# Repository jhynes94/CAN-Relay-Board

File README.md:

# CAN-Relay-Board
CAN controlled Relay board for automotive applications

## Items to complete
1. Detemine Relay to use for design (based on Current(A)/Costs constraints).
2. Design better interface board to use Arduino Nano Programmer
    1. JST Connector to Arduino Development Board
    2. 2.54mm Connector with standard interface board
    3. Consider adding UART connector as well.
3. Determine modes needed for device
    1. CAN ID changing?
    2. CAN Mode changing?
    3. How this should be modified? (DIP swich or via SW)

## Development Setup

Programming the ATTiny is a bit difficult. Setup can be completed using the following tutorial:
https://youtu.be/AL9vK_xMt4E

The library used for SPI enabled CAN device:
https://github.com/autowp/arduino-mcp2515

PEAK CAN usb device is used for interfacing and development. The software to run this is called <b>pcanview<b>

## Far Future items

Future Tutorial for programming an alternative way:
https://www.youtube.com/watch?v=ra7bT74EGUs

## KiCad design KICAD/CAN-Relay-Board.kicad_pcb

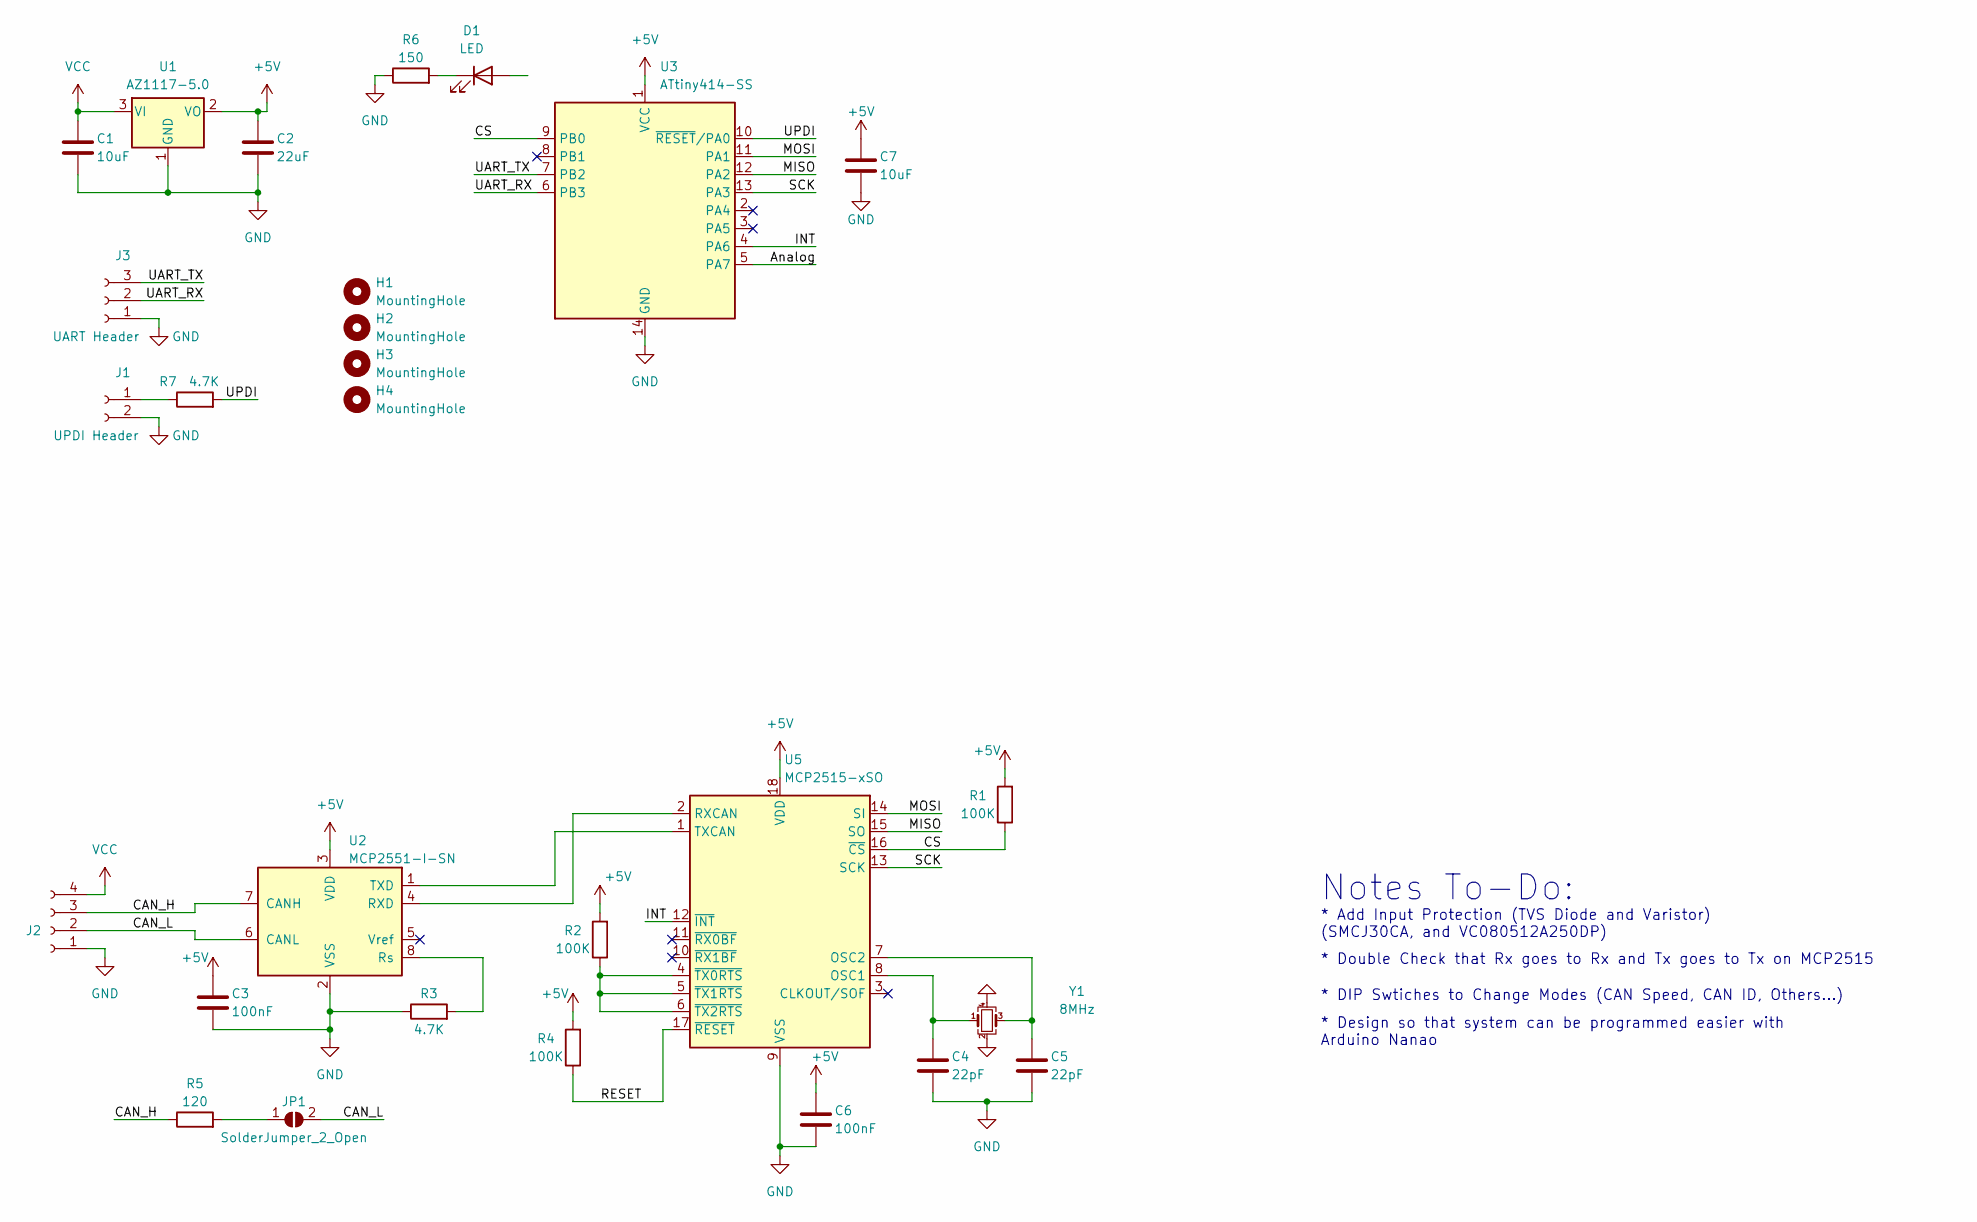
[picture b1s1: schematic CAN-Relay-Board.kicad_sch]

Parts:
C1, C7: 10uF; C_0805_2012Metric_Pad1.18x1.45mm_HandSolder; Manufacturer PN CL21A106KOQNNNE; Digi-Key PN 1276-1096-2-ND
C2: 22uF; C_0805_2012Metric_Pad1.18x1.45mm_HandSolder; Manufacturer PN CL21A226MOCLRNC; Digi-Key PN 1276-6780-1-ND
C3, C6: 100nF; C_0603_1608Metric_Pad1.08x0.95mm_HandSolder; Manufacturer PN CL10B104KB8NNNC; Digi-Key PN 1276-1000-1-ND
C4, C5: 22pF; C_0603_1608Metric_Pad1.08x0.95mm_HandSolder; Manufacturer PN CC0603JRNPO9BN220; Digi-Key PN 311-1062-1-ND
D1: LED; LED_0603_1608Metric_Pad1.05x0.95mm_HandSolder; Manufacturer PN LTST-C191KGKT; Digi-Key PN 160-1446-1-ND
H1, H2, H3, H4: MountingHole; MountingHole_2.2mm_M2_ISO14580
J1: UPDI Header; PinHeader_1x02_P1.27mm_Vertical
J2: Conn_01x04_Female; PinHeader_1x04_P1.27mm_Vertical
J3: UART Header; PinHeader_1x03_P1.27mm_Vertical
JP1: SolderJumper_2_Open; SolderJumper-2_P1.3mm_Open_TrianglePad1.0x1.5mm
R1, R2, R4: 100K; R_0603_1608Metric_Pad0.98x0.95mm_HandSolder; Manufacturer PN RC0603FR-07100KL; Digi-Key PN 311-100KHRCT-ND
R3, R7: 4.7K; R_0603_1608Metric_Pad0.98x0.95mm_HandSolder; Manufacturer PN RC0402JR-074K7L; Digi-Key PN 311-4.7KJRCT-ND
R5: 120; R_1206_3216Metric_Pad1.30x1.75mm_HandSolder; Manufacturer PN AC1206FR-07120RL; Digi-Key PN YAG3810CT-ND
R6: 150; R_0603_1608Metric_Pad0.98x0.95mm_HandSolder; Manufacturer PN RC0603FR-07150RL; Digi-Key PN 311-150HRCT-ND
U1: AZ1117-5.0; SOT-223-3_TabPin2; Manufacturer PN AZ1117IH-5.0TRG1; Digi-Key PN AZ1117IH-5.0TRG1DICT-ND
U2: MCP2551-I-SN; SOIC-8_3.9x4.9mm_P1.27mm
U3: ATtiny414-SS; SOIC-14_3.9x8.7mm_P1.27mm; Manufacturer PN ATTINY414-SSNR; Digi-Key PN ATTINY414-SSNRCT-ND
U5: MCP2515-xSO; SOIC-18W_7.5x11.6mm_P1.27mm; Manufacturer PN MCP2515-I/SO; Digi-Key PN MCP2515-I/SO-ND
Y1: 8MHz; Crystal_SMD_3225-4Pin_3.2x2.5mm_HandSoldering; Manufacturer PN ECS-80-8-33-JEN-TR3; Digi-Key PN 50-ECS-80-8-33-JEN-TR3CT-ND

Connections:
+5V: C2.1, C3.1, C6.1, C7.1, R1.2, R2.2, R4.2, U1.2 (VO), U2.3 (VDD), U3.1 (VCC), U5.18 (VDD)
/Analog: U3.5 (PA7)
/CAN_H: J2.3, R5.1, U2.7 (CANH)
/CAN_L: J2.2, JP1.2 (B), U2.6 (CANL)
/CS: R1.1, U3.9 (PB0), U5.16 (~CS)
/INT: U3.4 (PA6), U5.12 (~INT)
/MISO: U3.12 (PA2), U5.15 (SO)
/MOSI: U3.11 (PA1), U5.14 (SI)
/RESET: R4.1, U5.17 (~RESET)
/SCK: U3.13 (PA3), U5.13 (SCK)
/UART_RX: J3.2, U3.6 (PB3)
/UART_TX: J3.3, U3.7 (PB2)
/UPDI: R7.2, U3.10 (~RESET/PA0)
GND: C1.2, C2.2, C3.2, C4.2, C5.2, C6.2, C7.2, J1.2, J2.1, J3.1, R3.1, R6.1, U1.1 (GND), U2.2 (VSS), U3.14 (GND), U5.9 (VSS), Y1.2, Y1.4
unnamed: C4.1, U5.8 (OSC1), Y1.1
unnamed: C5.1, U5.7 (OSC2), Y1.3
unnamed: D1.1 (K), R6.2
unnamed: J1.1, R7.1
unnamed: JP1.1 (A), R5.2
unnamed: R2.1, U5.4 (~TX0RTS), U5.5 (~TX1RTS), U5.6 (~TX2RTS)
unnamed: R3.2, U2.8 (Rs)
unnamed: U2.1 (TXD), U5.1 (TXCAN)
unnamed: U2.4 (RXD), U5.2 (RXCAN)
VCC: C1.1, J2.4, U1.3 (VI)

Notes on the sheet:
* Add Input Protection (TVS Diode and Varistor) (SMCJ30CA, and VC080512A250DP)
* Design so that system can be programmed easier with Arduino Nanao
* Double Check that Rx goes to Rx and Tx goes to Tx on MCP2515
Notes To-Do:
* DIP Swtiches to Change Modes (CAN Speed, CAN ID, Others...)

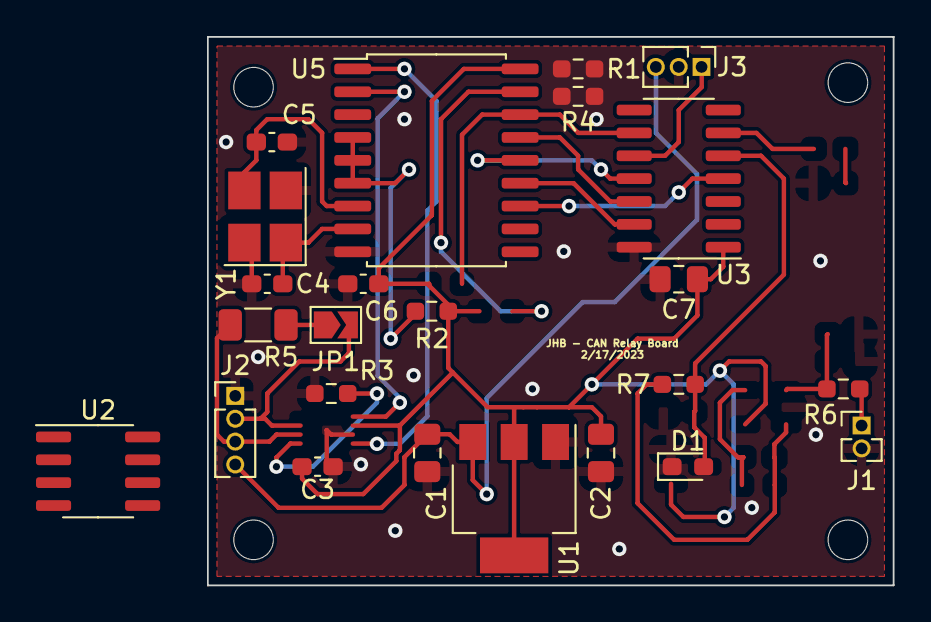
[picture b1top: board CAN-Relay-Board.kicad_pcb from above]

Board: 2 copper layers, 38.1 x 30.5 mm, 28 parts (0 on the bottom side), 23 nets.

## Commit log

2023-02-18 Update from alt design for Relay board
2023-02-23 Schematic 90% complete
